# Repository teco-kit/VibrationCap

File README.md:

# VibrationCap

This repository contains the schematic and board files for the hardware used in the paper *"[VibrationCap: Studying Vibrotactile Localization on the Human Head with an Unobtrusive Wearable Tactile Display](https://dl.acm.org/citation.cfm?doid=3123021.3123047 "VibrationCap")"* presented at the [ISWC '17](http://iswc.net/iswc17/ "ISWC 2017 Homepage") in Maui, Hawaii.

If you use this hardware as part of your work, please consider [citing our paper](https://dl.acm.org/citation.cfm?doid=3123021.3123047 "VibrationCap").

## Contents

### Hardware
Schematics/Board files for the _BLE Module_ and _Vibration Module_. Can be opened in the free version of _EAGLE_.

### Firmware
Firmware for programming the RedBear BLE Nano on the _BLE Module_. Can be opened in the _Arduino IDE_.

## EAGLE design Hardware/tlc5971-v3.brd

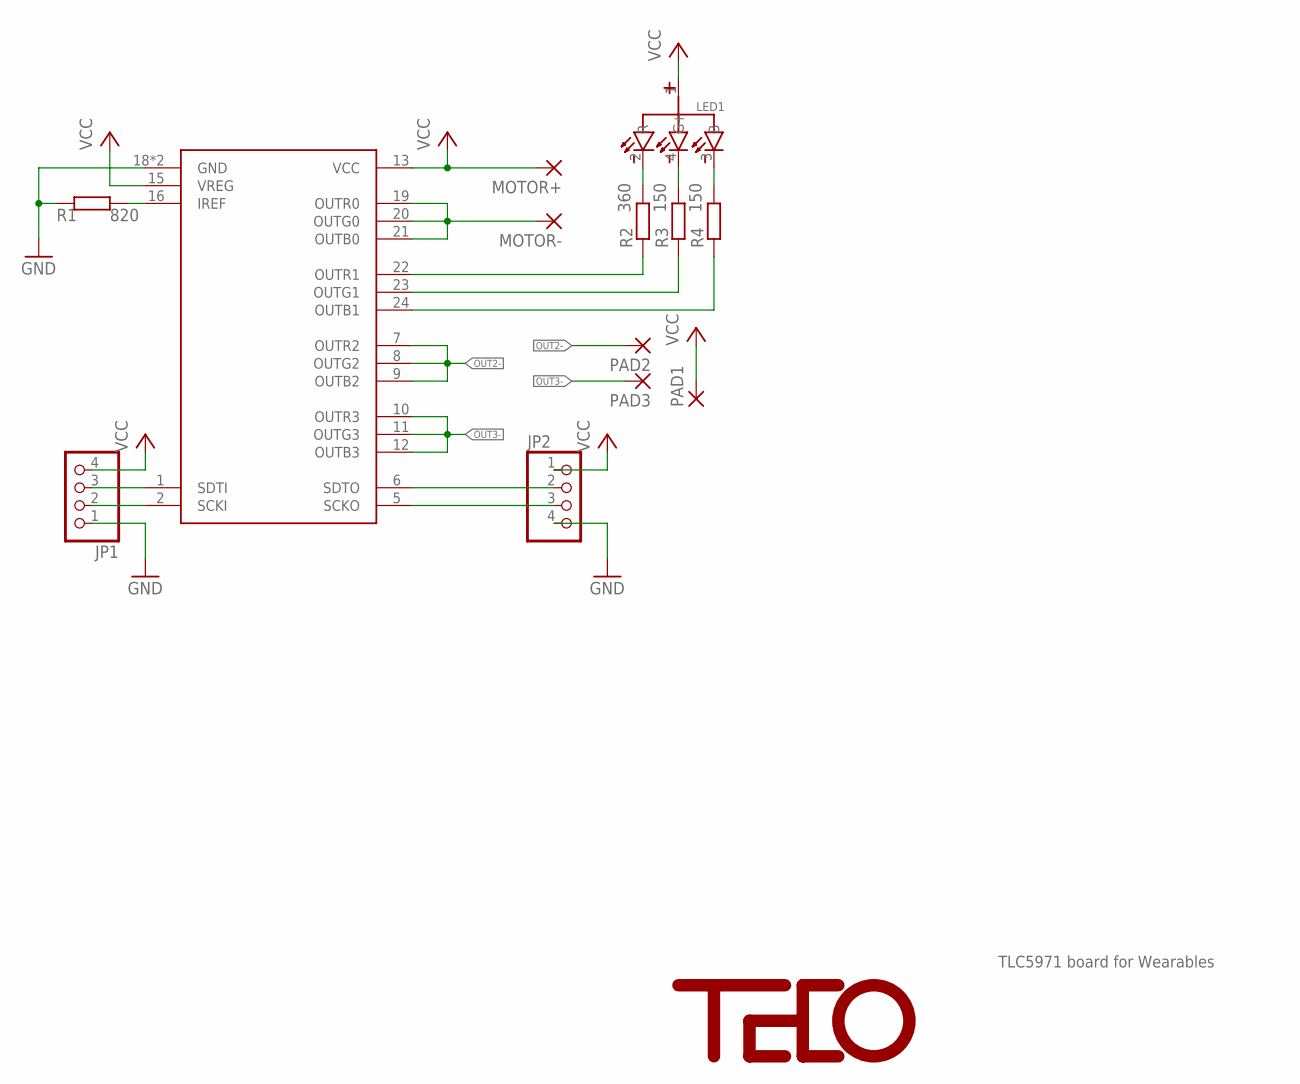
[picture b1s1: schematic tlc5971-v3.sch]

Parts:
JP1, JP2: PINHD-1X4; 1X04
LED1: SML-LX0404SIUPGUSB; SML_LED
MOTOR+: SMD2; SMD1,27-2,54
MOTOR-: SMD2; SMD1,27-2,54
PAD1, PAD2, PAD3: SMD2; SMD1,27-2,54
R1: 820; R0402
R2: 360; R0402
R3, R4: 150; R0402
U$1: TLC5971; RGE.24
U$3: TECO-LOGO-BIG

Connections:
GND: JP1.1, JP2.4, R1.1, U$1.18 (GND), U$1.PAD (GND)
unnamed: LED1.2 (R), R2.2
unnamed: R1.2, U$1.16 (IREF)
unnamed: JP1.3, U$1.1 (SDTI)
unnamed: JP1.2, U$1.2 (SCKI)
unnamed: JP2.2, U$1.6 (SDTO)
unnamed: JP2.3, U$1.5 (SCKO)
unnamed: LED1.4 (G), R3.2
unnamed: LED1.3 (B), R4.2
unnamed: R2.1, U$1.22 (OUTR1)
unnamed: R3.1, U$1.23 (OUTG1)
unnamed: R4.1, U$1.24 (OUTB1)
OUT0-: MOTOR-.1, U$1.19 (OUTR0), U$1.20 (OUTG0), U$1.21 (OUTB0)
OUT2-: PAD2.1, U$1.7 (OUTR2), U$1.8 (OUTG2), U$1.9 (OUTB2)
OUT3-: PAD3.1, U$1.10 (OUTR3), U$1.11 (OUTG3), U$1.12 (OUTB3)
VCC: JP1.4, JP2.1, LED1.1 (+), MOTOR+.1, PAD1.1, U$1.13 (VCC), U$1.15 (VREG)

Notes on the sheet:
TLC5971 board for Wearables

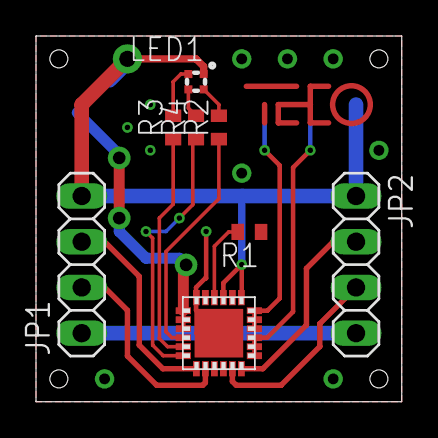
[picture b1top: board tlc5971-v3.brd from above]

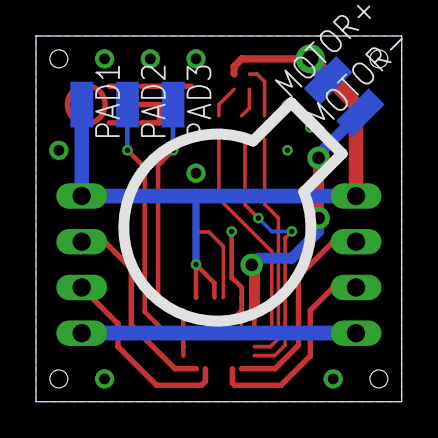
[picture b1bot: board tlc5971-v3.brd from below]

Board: 2 copper layers, 20.3 x 20.3 mm, 14 parts (5 on the bottom side), 16 nets.

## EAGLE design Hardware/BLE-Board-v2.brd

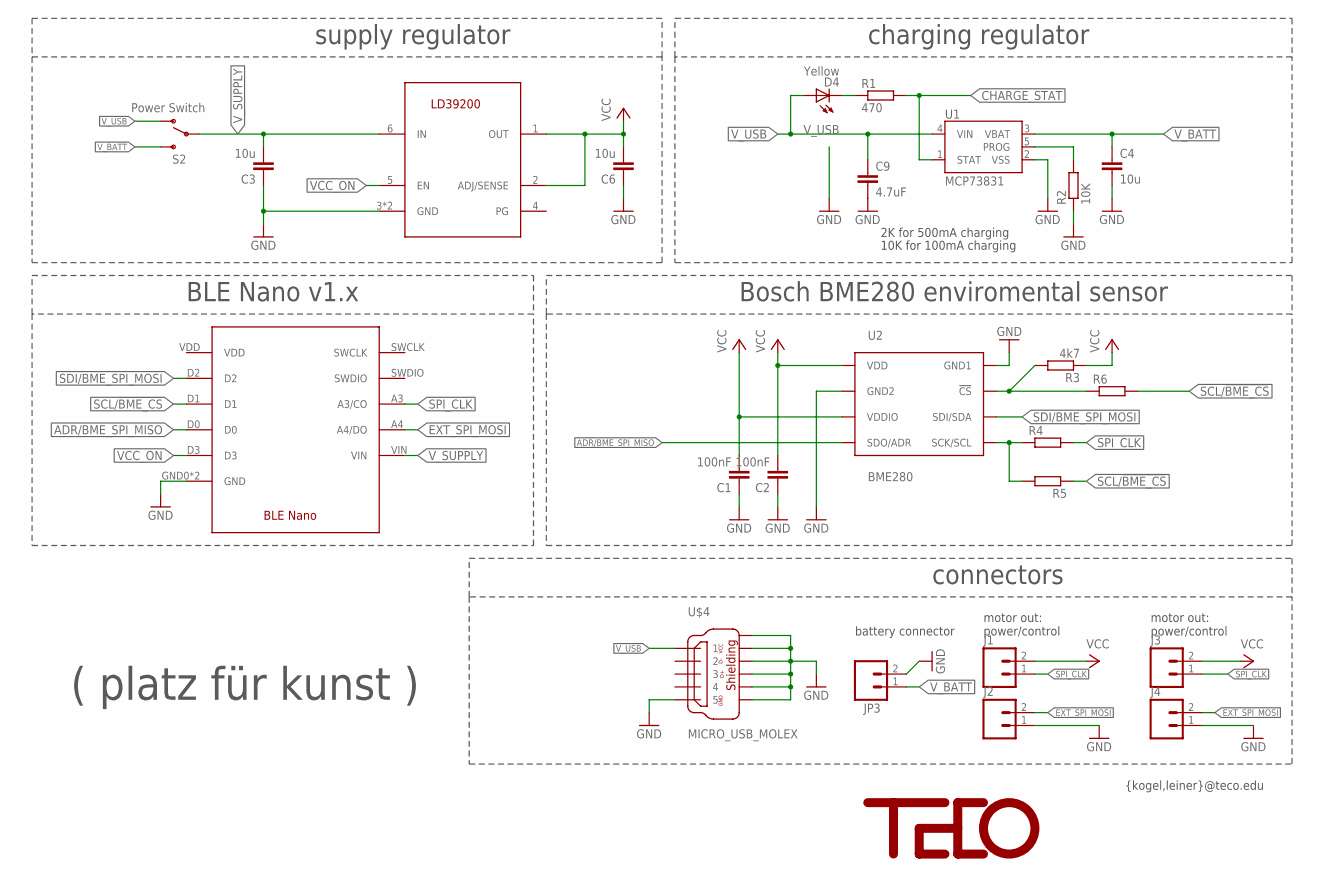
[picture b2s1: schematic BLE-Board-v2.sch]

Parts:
C1, C2: 100nF; C0603K
C3, C4, C6: 10u; C0603K
C9: 4.7uF; C0603K
D4: Yellow; LED-0603
J1, J2, J3, J4: M02PTH; 1X02
JP3: M02-JST-2MM-SMT; JST-2-SMD
R1: 470; R0402
R2: 10K; R0402
R3: 4k7; R0402
R4, R5, R6: R-EU_R0201; R0201
S2: Power Switch; AYZ0202
U1: MCP73831; SOT23-5
U2: BME280; BME280_LGA
U$1: BLE-NANO
U$2: LD39200DNF6; DFN6-3X3
U$3: TECO-LOGO-BIG
U$4: MICRO_USB_MOLEX

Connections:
ADR/BME_SPI_MISO: U2.P$5 (SDO/ADR), U$1.D0
CHARGE_STAT: R1.2, U1.1 (STAT)
EXT_SPI_MOSI: J2.2, J4.2, U$1.A4 (A4/DO)
GND: C1.1, C2.1, C3.1, C4.2, C6.1, C9.2, J2.1, J4.1, JP3.2, R2.1, U1.2 (VSS), U2.P$1 (GND1), U2.P$7 (GND2), U$1.GND0 (GND), U$1.GND1 (GND), U$2.3 (GND), U$2.EXP (GND), U$4.5, U$4.SHIELD@1, U$4.SHIELD@2, U$4.SHIELD@3, U$4.SHIELD@4, U$4.SHIELD@5, U$4.SHIELD@6
unnamed: D4.C, R1.1
unnamed: R4.1, R5.2, U2.P$4 (SCK/SCL)
unnamed: R3.2, R6.1, U2.P$2 (!CS)
unnamed: R2.2, U1.5 (PROG)
SCL/!BME_CS: R5.1, R6.2, U$1.D1
SDI/BME_SPI_MOSI: U2.P$3 (SDI/SDA), U$1.D2
SPI_CLK: J1.1, J3.1, R4.2, U$1.A3 (A3/CO)
VCC: C1.2, C2.2, C6.2, J1.2, J3.2, R3.1, U2.P$6 (VDDIO), U2.P$8 (VDD), U$2.1 (OUT), U$2.2 (ADJ/SENSE)
VCC_ON: U$1.D3, U$2.5 (EN)
V_BATT: C4.1, JP3.1, S2.3 (S), U1.3 (VBAT)
V_SUPPLY: C3.2, S2.2, U$1.VIN, U$2.6 (IN)
V_USB: C9.1, D4.A, S2.1 (O), U1.4 (VIN), U$4.1

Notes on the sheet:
battery connector
{kogel,leiner}@teco.edu
Bosch BME280 enviromental sensor
motor out: power/control
connectors
BLE Nano v1.x
2K for 500mA charging
10K for 100mA charging
charging regulator
supply regulator
( platz für kunst )

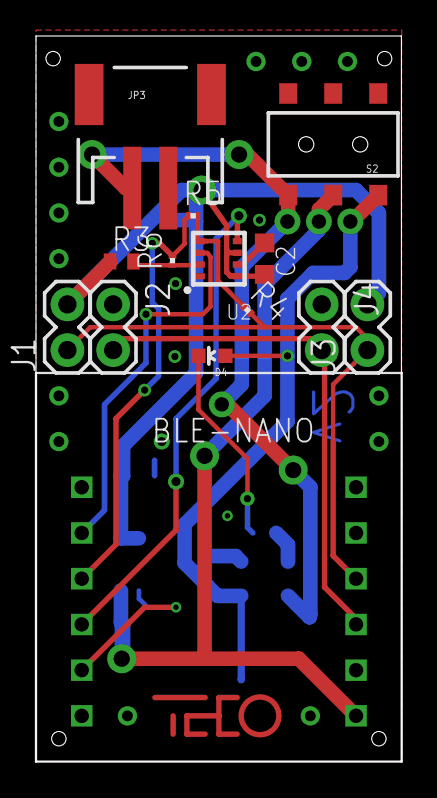
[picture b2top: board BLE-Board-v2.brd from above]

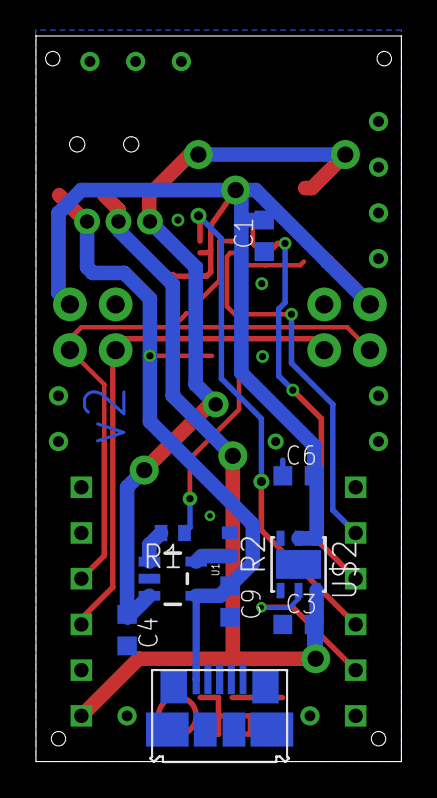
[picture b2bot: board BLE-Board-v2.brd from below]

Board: 2 copper layers, 20.3 x 40.3 mm, 25 parts (10 on the bottom side), 16 nets.

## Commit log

2017-09-07 Create LICENSE
2017-09-07 Initial commit.

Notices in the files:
parts and their libraries:
SparkFun-Connectors: Licensing: Creative Commons ShareAlike 4.0 International - https://creativecommons.org/licenses/by-sa/4.0
